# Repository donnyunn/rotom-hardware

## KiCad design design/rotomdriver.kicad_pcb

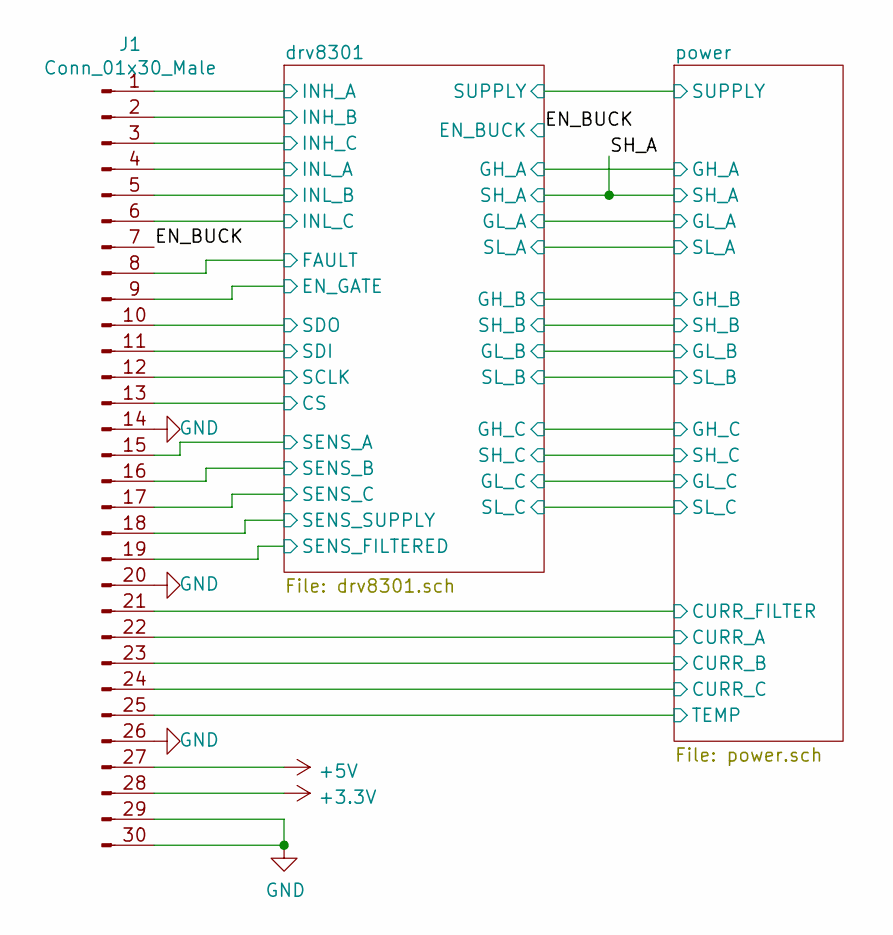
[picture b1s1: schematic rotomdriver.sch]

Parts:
J1: Conn_01x30_Male; PinHeader_2x15_P2.54mm_Vertical

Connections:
+3V3: J1.28; also elsewhere on the board
+5V: J1.27; also elsewhere on the board
/EN_BUCK: J1.7; also elsewhere on the board
/drv8301/CS: J1.13; also elsewhere on the board
/drv8301/EN_GATE: J1.9; also elsewhere on the board
/drv8301/FAULT: J1.8; also elsewhere on the board
/drv8301/INH_A: J1.1; also elsewhere on the board
/drv8301/INH_B: J1.2; also elsewhere on the board
/drv8301/INH_C: J1.3; also elsewhere on the board
/drv8301/INL_A: J1.4; also elsewhere on the board
/drv8301/INL_B: J1.5; also elsewhere on the board
/drv8301/INL_C: J1.6; also elsewhere on the board
/drv8301/SCLK: J1.12; also elsewhere on the board
/drv8301/SDI: J1.11; also elsewhere on the board
/drv8301/SDO: J1.10; also elsewhere on the board
/drv8301/SENS_A: J1.15; also elsewhere on the board
/drv8301/SENS_B: J1.16; also elsewhere on the board
/drv8301/SENS_C: J1.17; also elsewhere on the board
/drv8301/SENS_FILTERED: J1.19; also elsewhere on the board
/drv8301/SENS_SUPPLY: J1.18; also elsewhere on the board
/power/CURR_A: J1.22; also elsewhere on the board
/power/CURR_B: J1.23; also elsewhere on the board
/power/CURR_C: J1.24; also elsewhere on the board
/power/CURR_FILTER: J1.21; also elsewhere on the board
/power/TEMP: J1.25; also elsewhere on the board
GND: J1.14, J1.20, J1.26, J1.29, J1.30; also elsewhere on the board

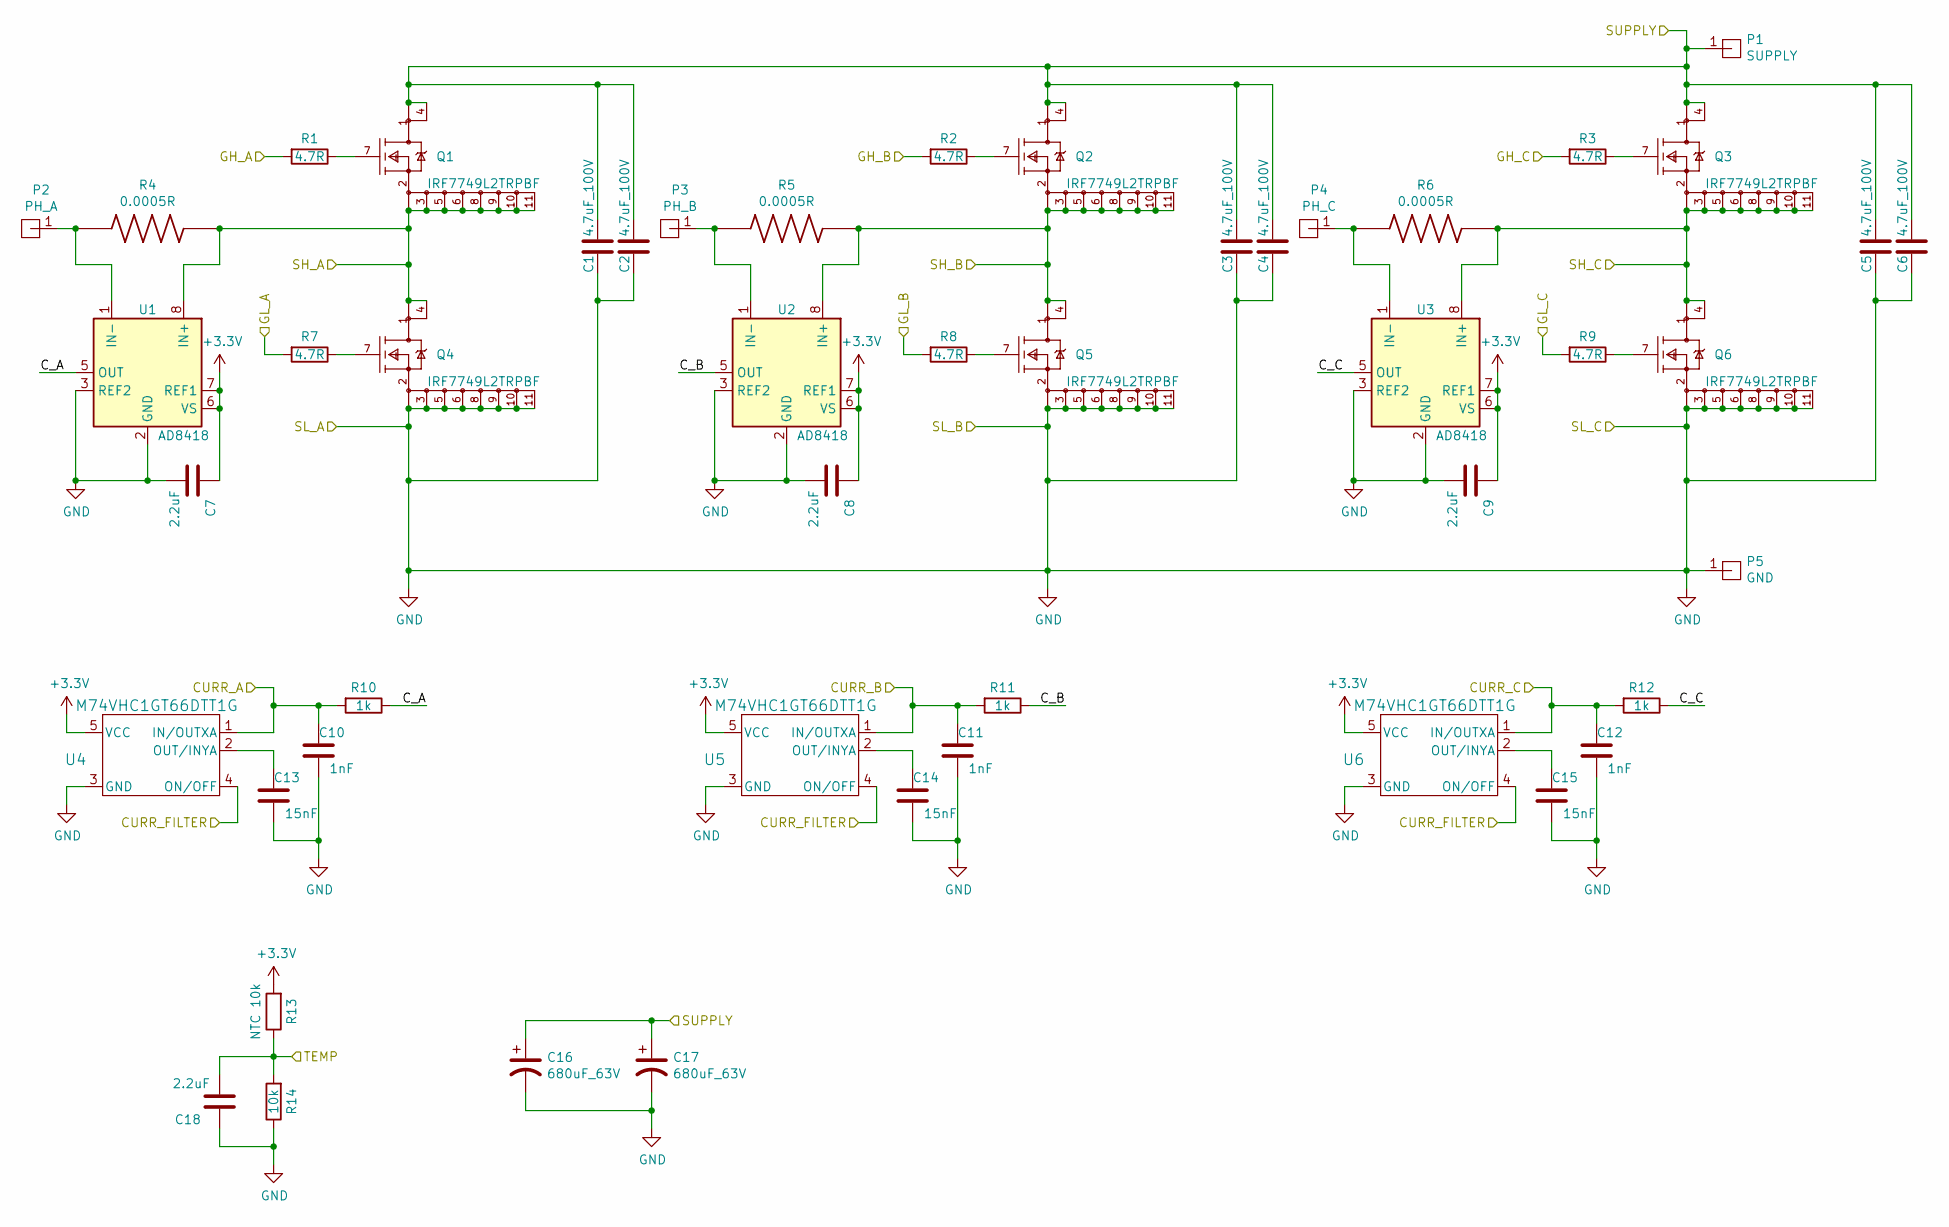
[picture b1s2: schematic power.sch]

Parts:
C1, C2, C3, C4, C5, C6: 4.7uF_100V; C_1210_3225Metric; MPN CL32B475KCVZW6E
C7, C8, C9, C18: 2.2uF; C_0603_1608Metric; MPN CL10A225KQ8NNNC
C10, C11, C12: 1nF; C_0603_1608Metric; MPN CML0603C0G1R0CT50V
C13, C14, C15: 15nF; C_0603_1608Metric; MPN CL10B153KB8NNNC
C16, C17: 680uF_63V; CP_Elec_18x22; MPN AFK687M63R44T-F
P1: SUPPLY; HighCurrent_WithHoles_400mils
P2: PH_A; HighCurrent_WithHoles_250mils
P3: PH_B; HighCurrent_WithHoles_250mils
P4: PH_C; HighCurrent_WithHoles_250mils
P5: GND; HighCurrent_WithHoles_400mils
Q1, Q2, Q3, Q4, Q5, Q6: IRF7749L2TRPBF; Infineon-IRF7749L2TRPBF-0-0-0; MPN IRF7749L2TRPBF
R1, R2, R3, R7, R8, R9: 4.7R; R_0603_1608Metric; MPN RMCF0603FT4K70
R4, R5, R6: 0.0005R; RESC3216X105N; MPN HCS1206FTL500
R10, R11, R12: 1k; R_0603_1608Metric; MPN RMCF0603JJ1K00
R13: NTC 10k; R_0603_1608Metric; MPN NCP18XH103F03RB
R14: 10k; R_0603_1608Metric; MPN RNCF0603BTE10K0
U1, U2, U3: AD8418; MSOP-8_3x3mm_P0.65mm; MPN AD8418ABRMZ-RL
U4, U5, U6: M74VHC1GT66DTT1G; MPN M74VHC1GT66DTT1G

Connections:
+3V3: C7.1, C8.1, C9.1, R13.2, U1.6 (VS), U1.7 (REF1), U2.6 (VS), U2.7 (REF1), U3.6 (VS), U3.7 (REF1), U4.5 (VCC), U5.5 (VCC), U6.5 (VCC); also elsewhere on the board
/SH_A: Q1.2 (S), Q1.3 (S), Q1.5 (S), Q1.6 (S), Q1.8 (S), Q1.9 (S), Q1.10 (S), Q1.11 (S), Q4.1 (D), Q4.4 (D), R4.2, U1.8 (IN+); also elsewhere on the board
/drv8301/GH_A: R1.2; also elsewhere on the board
/drv8301/GH_B: R2.2; also elsewhere on the board
/drv8301/GH_C: R3.2; also elsewhere on the board
/drv8301/GL_A: R7.2; also elsewhere on the board
/drv8301/GL_B: R8.2; also elsewhere on the board
/drv8301/GL_C: R9.2; also elsewhere on the board
/drv8301/SH_B: Q2.2 (S), Q2.3 (S), Q2.5 (S), Q2.6 (S), Q2.8 (S), Q2.9 (S), Q2.10 (S), Q2.11 (S), Q5.1 (D), Q5.4 (D), R5.2, U2.8 (IN+); also elsewhere on the board
/drv8301/SH_C: Q3.2 (S), Q3.3 (S), Q3.5 (S), Q3.6 (S), Q3.8 (S), Q3.9 (S), Q3.10 (S), Q3.11 (S), Q6.1 (D), Q6.4 (D), R6.2, U3.8 (IN+); also elsewhere on the board
/power/CURR_A: C10.2, R10.2, U4.1 (IN/OUTXA); also elsewhere on the board
/power/CURR_B: C11.2, R11.2, U5.1 (IN/OUTXA); also elsewhere on the board
/power/CURR_C: C12.2, R12.2, U6.1 (IN/OUTXA); also elsewhere on the board
/power/CURR_FILTER: U4.4 (ON/OFF), U5.4 (ON/OFF), U6.4 (ON/OFF); also elsewhere on the board
/power/C_A: R10.1, U1.5 (OUT)
/power/C_B: R11.1, U2.5 (OUT)
/power/C_C: R12.1, U3.5 (OUT)
/power/TEMP: C18.2, R13.1, R14.2; also elsewhere on the board
GND: C1.2, C2.2, C3.2, C4.2, C5.2, C6.2, C7.2, C8.2, C9.2, C10.1, C11.1, C12.1, C13.1, C14.1, C15.1, C16.2, C17.2, C18.1, P5.1, Q4.2 (S), Q4.3 (S), Q4.5 (S), Q4.6 (S), Q4.8 (S), Q4.9 (S), Q4.10 (S), Q4.11 (S), Q5.2 (S), Q5.3 (S), Q5.5 (S), Q5.6 (S), Q5.8 (S), Q5.9 (S), Q5.10 (S), Q5.11 (S), Q6.2 (S), Q6.3 (S), Q6.5 (S), Q6.6 (S), Q6.8 (S), Q6.9 (S), Q6.10 (S), Q6.11 (S), R14.1, U1.2 (GND), U1.3 (REF2), U2.2 (GND), U2.3 (REF2), U3.2 (GND), U3.3 (REF2), U4.3 (GND), U5.3 (GND), U6.3 (GND); also elsewhere on the board
unnamed: C13.2, U4.2 (OUT/INYA)
unnamed: C14.2, U5.2 (OUT/INYA)
unnamed: C15.2, U6.2 (OUT/INYA)
unnamed: P2.1, R4.1, U1.1 (IN-)
unnamed: P3.1, R5.1, U2.1 (IN-)
unnamed: P4.1, R6.1, U3.1 (IN-)
unnamed: Q1.7 (G), R1.1
unnamed: Q2.7 (G), R2.1
unnamed: Q3.7 (G), R3.1
unnamed: Q4.7 (G), R7.1
unnamed: Q5.7 (G), R8.1
unnamed: Q6.7 (G), R9.1
SUPPLY: C1.1, C2.1, C3.1, C4.1, C5.1, C6.1, C16.1, C17.1, P1.1, Q1.1 (D), Q1.4 (D), Q2.1 (D), Q2.4 (D), Q3.1 (D), Q3.4 (D); also elsewhere on the board

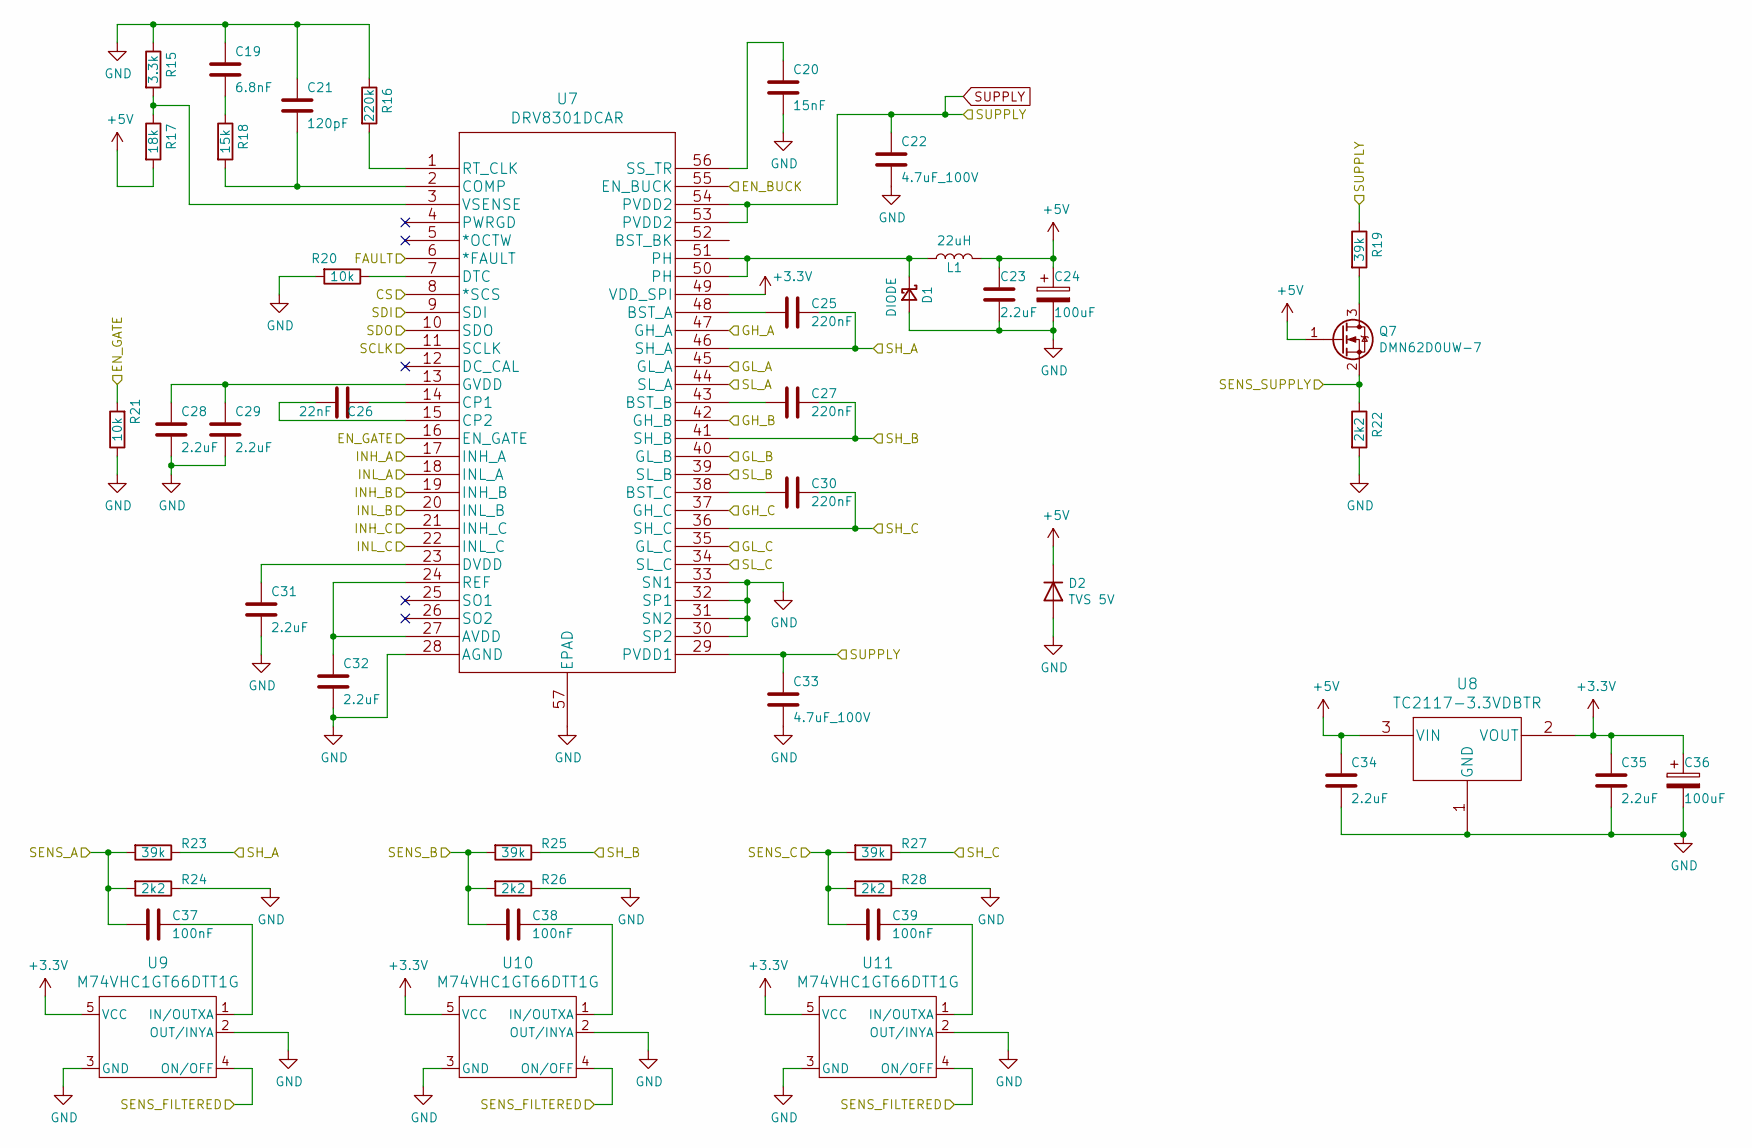
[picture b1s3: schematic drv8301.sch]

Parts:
C19: 6.8nF; C_0603_1608Metric; MPN CL10B682KC8WPNC
C20: 15nF; C_0603_1608Metric; MPN CL10B153KO8NNNC
C21: 120pF; C_0603_1608Metric; MPN CL10C121JB8NNNC
C22, C33: 4.7uF_100V; C_0603_1608Metric; MPN CL32B475KCVZW6E
C23, C28, C29, C31, C32, C34, C35: 2.2uF; C_0603_1608Metric; MPN CL10A225KP8NNNC
C24, C36: 100uF; CP_EIA-6032-20_AVX-F; MPN TAJW107K006RNJ
C25, C27, C30: 220nF; C_0603_1608Metric; MPN CL03A224KP3NNNC
C26: 22nF; C_0603_1608Metric; MPN CL10B223KB8WPNC
C37, C38, C39: 100nF; C_0603_1608Metric; MPN CL10B104KB8NNNL
D1: DIODE; D_SOD-123; MPN PMEG6020ER,115
D2: TVS 5V; D_SMA; MPN SMAJ5.0A
L1: 22uH; L_Bourns-SRN8040_8x8.15mm; MPN SDR0805-220ML
Q7: DMN62D0UW-7; SOT-323_SC-70
R15: 3.3k; R_0603_1608Metric; MPN CPF-A-0603B3K3E
R16: 220k; R_0603_1608Metric; MPN CRGCQ0603F220K
R17: 18k; R_0603_1608Metric; MPN CRGCQ0603F18K
R18: 15k; R_0603_1608Metric; MPN CRGCQ0603F15K
R19: 39k; R_0603_1608Metric; MPN CPF0603B39KE1
R20, R21: 10k; R_0603_1608Metric; MPN RNCP0603FTD10K0
R22, R24, R26, R28: 2k2; R_0603_1608Metric; MPN CPF-A-0603B2K2E
R23, R25, R27: 39k; R_0603_1608Metric; MPN ERJ-3EKF3902V
U7: DRV8301DCAR; HTSSOP-56-1EP_6.1x14mm_P0.5mm_EP3.61x6.35mm; MPN DRV8301DCAR
U8: TC2117-3.3VDBTR; SOT-223-3_TabPin2; MPN TC2117-3.3VDBTR
U9, U10, U11: M74VHC1GT66DTT1G; MPN M74VHC1GT66DTT1G

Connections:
+3V3: C35.1, C36.1, U7.49 (VDD_SPI), U8.2 (VOUT), U9.5 (VCC), U10.5 (VCC), U11.5 (VCC); also elsewhere on the board
+5V: C23.1, C24.1, C34.1, D2.1 (K), L1.2, Q7.1 (G), R17.2, U8.3 (VIN); also elsewhere on the board
/EN_BUCK: U7.55 (EN_BUCK); also elsewhere on the board
/SH_A: C25.2, R23.1, U7.46 (SH_A); also elsewhere on the board
/drv8301/CS: U7.8 (*SCS); also elsewhere on the board
/drv8301/EN_GATE: R21.2, U7.16 (EN_GATE); also elsewhere on the board
/drv8301/FAULT: U7.6 (*FAULT); also elsewhere on the board
/drv8301/GH_A: U7.47 (GH_A); also elsewhere on the board
/drv8301/GH_B: U7.42 (GH_B); also elsewhere on the board
/drv8301/GH_C: U7.37 (GH_C); also elsewhere on the board
/drv8301/GL_A: U7.45 (GL_A); also elsewhere on the board
/drv8301/GL_B: U7.40 (GL_B); also elsewhere on the board
/drv8301/GL_C: U7.35 (GL_C); also elsewhere on the board
/drv8301/INH_A: U7.17 (INH_A); also elsewhere on the board
/drv8301/INH_B: U7.19 (INH_B); also elsewhere on the board
/drv8301/INH_C: U7.21 (INH_C); also elsewhere on the board
/drv8301/INL_A: U7.18 (INL_A); also elsewhere on the board
/drv8301/INL_B: U7.20 (INL_B); also elsewhere on the board
/drv8301/INL_C: U7.22 (INL_C); also elsewhere on the board
/drv8301/SCLK: U7.11 (SCLK); also elsewhere on the board
/drv8301/SDI: U7.9 (SDI); also elsewhere on the board
/drv8301/SDO: U7.10 (SDO); also elsewhere on the board
/drv8301/SENS_A: C37.1, R23.2, R24.2; also elsewhere on the board
/drv8301/SENS_B: C38.1, R25.2, R26.2; also elsewhere on the board
/drv8301/SENS_C: C39.1, R27.2, R28.2; also elsewhere on the board
/drv8301/SENS_FILTERED: U9.4 (ON/OFF), U10.4 (ON/OFF), U11.4 (ON/OFF); also elsewhere on the board
/drv8301/SENS_SUPPLY: Q7.2 (S), R22.1; also elsewhere on the board
/drv8301/SH_B: C27.2, R25.1, U7.41 (SH_B); also elsewhere on the board
/drv8301/SH_C: C30.2, R27.1, U7.36 (SH_C); also elsewhere on the board
GND: C19.1, C20.2, C21.1, C22.2, C23.2, C24.2, C28.2, C29.2, C31.2, C32.2, C33.2, C34.2, C35.2, C36.2, D1.2 (A), D2.2 (A), R15.1, R16.1, R20.2, R21.1, R22.2, R24.1, R26.1, R28.1, U7.28 (AGND), U7.30 (SP2), U7.31 (SN2), U7.32 (SP1), U7.33 (SN1), U7.34 (SL_C), U7.39 (SL_B), U7.44 (SL_A), U7.57 (EPAD), U8.1 (GND), U9.2 (OUT/INYA), U9.3 (GND), U10.2 (OUT/INYA), U10.3 (GND), U11.2 (OUT/INYA), U11.3 (GND); also elsewhere on the board
unnamed: C19.2, R18.1
unnamed: C20.1, U7.56 (SS_TR)
unnamed: C21.2, R18.2, U7.2 (COMP)
unnamed: C25.1, U7.48 (BST_A)
unnamed: C26.1, U7.14 (CP1)
unnamed: C26.2, U7.15 (CP2)
unnamed: C27.1, U7.43 (BST_B)
unnamed: C28.1, C29.1, U7.13 (GVDD)
unnamed: C30.1, U7.38 (BST_C)
unnamed: C31.1, U7.23 (DVDD)
unnamed: C32.1, U7.24 (REF), U7.27 (AVDD)
unnamed: C37.2, U9.1 (IN/OUTXA)
unnamed: C38.2, U10.1 (IN/OUTXA)
unnamed: C39.2, U11.1 (IN/OUTXA)
unnamed: D1.1 (K), L1.1, U7.50 (PH), U7.51 (PH)
unnamed: Q7.3 (D), R19.2
unnamed: R15.2, R17.1, U7.3 (VSENSE)
unnamed: R16.2, U7.1 (RT_CLK)
unnamed: R20.1, U7.7 (DTC)
SUPPLY: C22.1, C33.1, R19.1, U7.29 (PVDD1), U7.53 (PVDD2), U7.54 (PVDD2); also elsewhere on the board

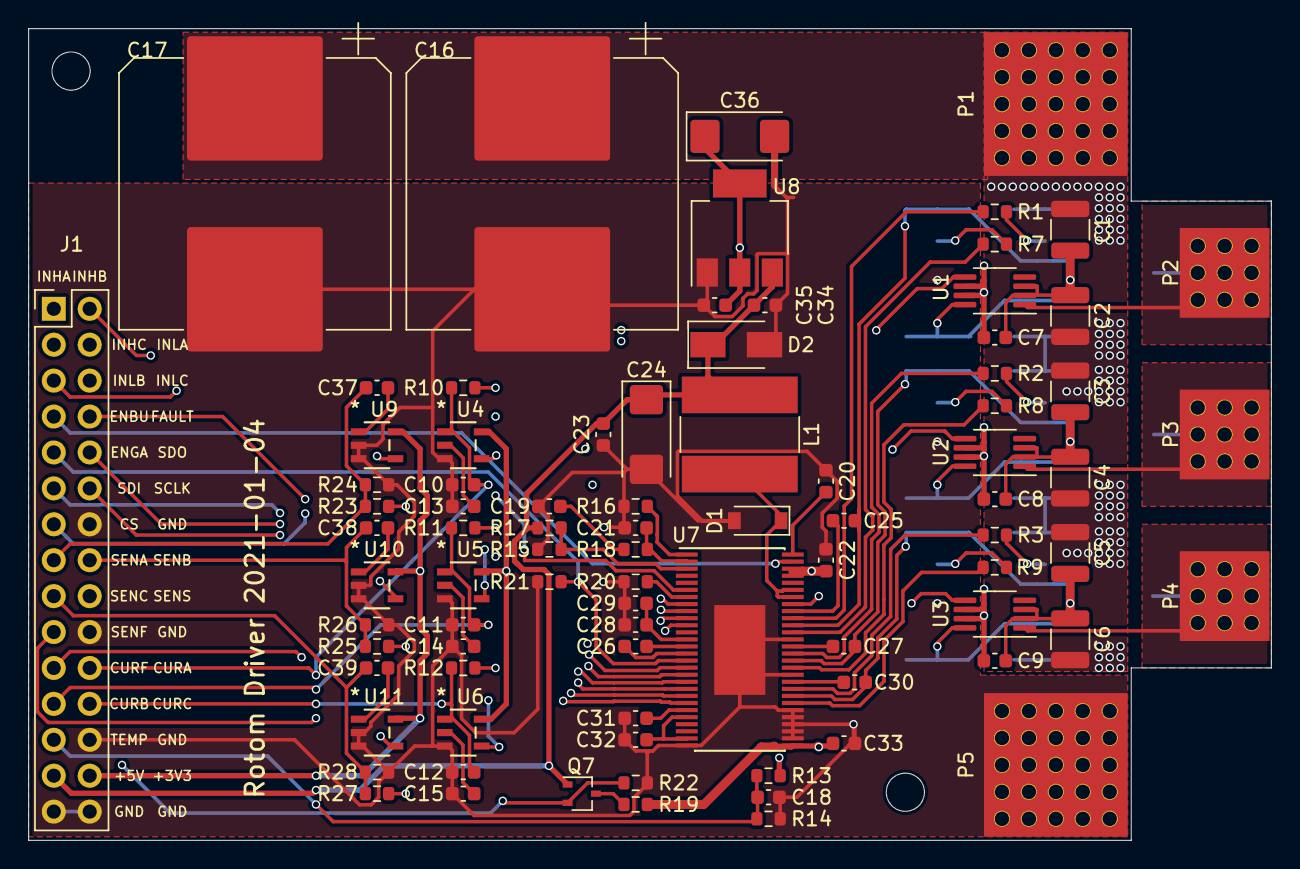
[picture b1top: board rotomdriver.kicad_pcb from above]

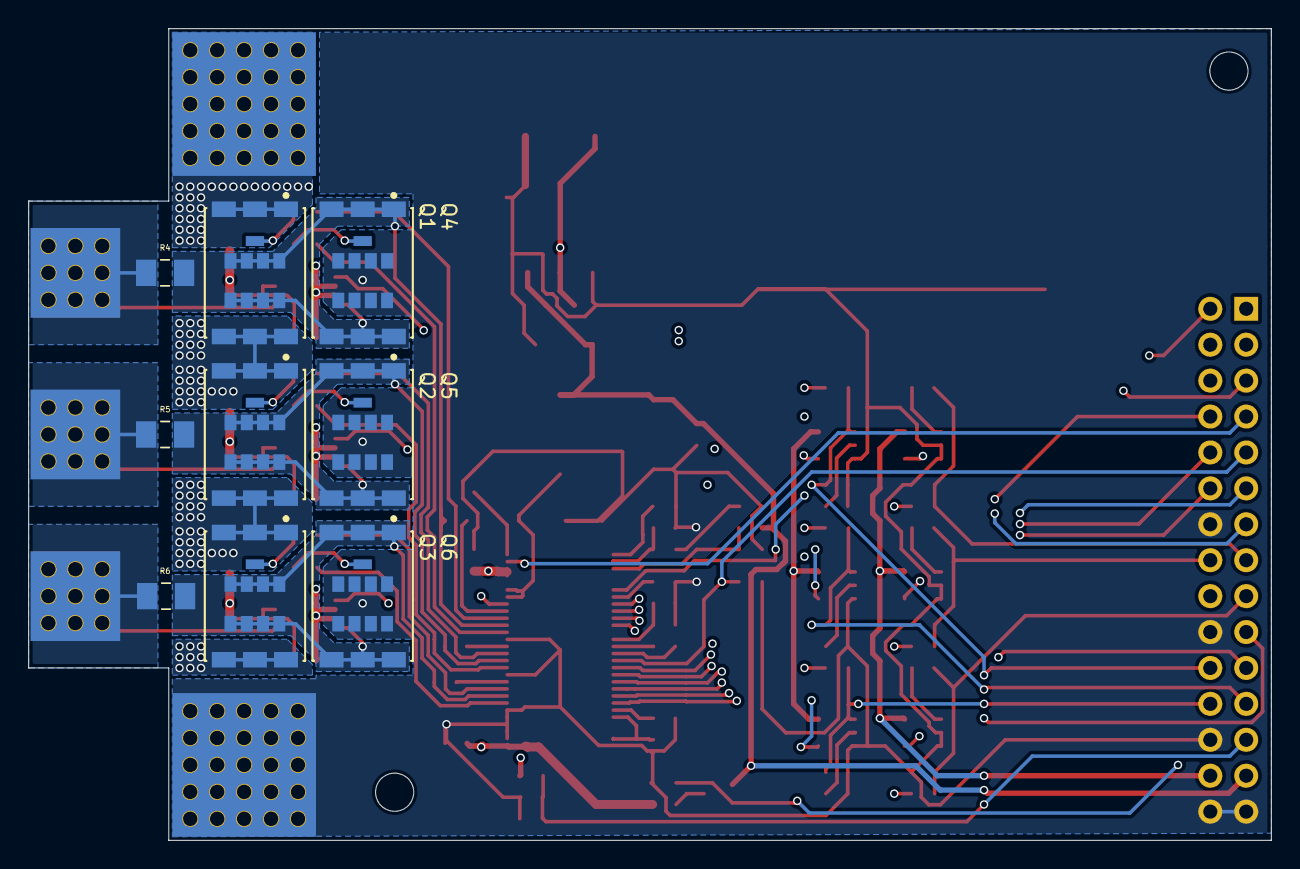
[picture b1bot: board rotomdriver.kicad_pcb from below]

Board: 4 copper layers, 87.9 x 57.4 mm, 94 parts (9 on the bottom side), 70 nets.

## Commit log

2020-12-11 design start
2020-12-16 power board design 1
2020-12-21 2020-12-21
2021-01-04 210104
2021-01-04 2021-01-04

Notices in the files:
parts and their libraries:
Copyright 2016 Accelerated Designs. All rights reserved.
